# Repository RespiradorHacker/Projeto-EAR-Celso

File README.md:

# e-AR (EAR) PROJECT - EMERGENCY VENTILATOR
This project was born because of CoVid19 pandemic.
The project Goal is to provide an emergency ventilator system to help CoVid19 serious cases using locally available resources. eAR was designed to meet specifications according to MHRA (UK) - Rapidly Manufactured Ventilator System and inspired by MIT E-Vent (USA) concepts and specs.

This is an OPEN HARDWARE - OPEN SOURCE PROJECT. 

DISCLAIMER: we will NOT take any responsability on devices built using partial or total information from this project. 
Any device used for life support and medical applications must meet all local requirements and they must be homologated by local regulatory agencies in ANY case.

The target is to run an entire ventilation system using an automotive car battery and an O2 can.
The initial project leader is Celso Ken Mori Monteiro, automotive designer with +30 yrs experience on automotive embedded systems
as OEM designer for customers as GM, Ford, VW, Fiat, Mercedes Benz, Scania, Navistar, Marcopolo, Agco...

The technology for first PCBs was downsized due to components availability in emerging countries so distributed production could be achieved even in small brazilian towns. The electronic parts are:
- PTH components
- Single-sided PCB, obtainable even by DIYs. 

Besides inclusive concept there is also a FR4 SMT version available for volume production.

Basic concepts:
- External FIO2 O2 + AIR mixer based on timed mechanical truck air valves and plastic bag container
- AMBU smasher based on car window motor due to availabilty and great mechanical characteristics. Motor reversion is necessary to allow dinamic changes of BPM, Tidal Volume, pressure ramping, I/E Ratio and Plateau Hold Time without ANY mechanical change.
- ECU based on Arduino Pro Mini (the most available in emerging countries) and SPI based IO expension
- 2 motor drive options: relay (need second adjustable supply or buck) and PWM driven mosfet driver

Project Evolution:
- full HW schematics and system component's description available on "EAR System Developer's HW Guide", portuguese only version
- PCB Gerbers available, Single Side PTH version, Motor driver on relay option only. Time and size were underestimated because we no longer use these old technologies. Released on March 30, 2020.
- Mech prototype phase 2 aproved, torque is OK and current is low.
- Gerbers of single sided boards on PTH components published on March 30, 2020. Time and size were underestimated because we no longer use these old technologies. 
- EAR System Developer's SW Guide released on March 30, 2020.
- Functional electronics prototype built and delivered on April 2, 2020. No changes in PCBs are necessary except hardware end-of-courses provided for EAR ECU Motor Driver Board. Test driven by firmware FW00 - focused on HW testing only. Reads input pots, control motor with reversal action, measures motor current and tests IO expansion board. All items are functional.
- FW00 published in April 3, 2020.
- Added Mosfet-based PWM Motor Driver and Absolute position sensor using a car fuel level sensor.
- First working mechanical+electrical prototype delivered in April 6, 2020.
- Added Pressure Sensor in April 7, 2020. First artificial lung is a balloon so first pressure profile was obtained. It Sounds promising.
- Firmware controls Tidal Volume and BPM according to Set Potentiometers. First functional firmware produce variable pressure ramps as needed, FW met 8-30 BPM dynamic range specification.
- Added motor cutoff in inspiratory phase according to pressure preset on pot Overpressure Threshold within 1cm H20 resolution.
- Added full mechanical design for functional AMBU compressing ARM in April 11, 2020
- Added in April 12, 2020: Motor Driver, mosfet NN version. Full Kicad design with schematics, PCB and Gerbers.
- Added in April 12,2020: eAR External watchdog Timer to increase eAR reliability. Full Eagle design with schematics, PCB and Gerbers.
- Added in April 13,2020: I/E selection (1:1, 1:2, 1:3 and 1:4) and Plateau Hold Time selection (150, 250, 500 and 1000ms hold on Plateau)
- Added in April 13,2020: Gol G3 tank level float sensor added as absolute position sensor. Increased linearity, resolution and availability
- Mech proto 3.2 added ball bearing in compression arm, currently performing cycling tests
- Added in April 15,2020; eAR Pressure sensor Board Design and PCB, MPX5010DP supported
- Added in April 21,2020: 10x10cm FR4 SMT single PCB design for volume production, verified design, send to production
- Added in April 21,2020: Mechanical proto 3.2 drawings delivered, functional design
- April 30, 2004: eAR FR4 Single-Board PCBs arrived, courtesy from Digicart/SC
- May 1st, 2020: eAR system reached 14 days of 24/7 operation, with 403,412 beathing cycles completed. eAR met minimum durability MHRA (UK) Spec with a prototype built on MDF, a window lift BDC motor and a 20-yrs-old chevy tank float sensor
- May 5, 2020: Multiple pressure sensor added, allowing almost any kind of linear pressure sensor to be connected to eAR system, including MPX5010, MPX10 almost all versions and packages including MPVZ and MP3V and experimental ultra-low-cost MPS20N0040D-S sensor
- May 12, 2020: Integrated EAR ECU tested, functional test OK. Some minor drilling errors corrected, some improvements done and new PCB generated. New mosfet driver option added in firmware as needed. Some components changed values due to standardization effort to ease production. eAR electronics is ready for mass production.
- May 23, 2020: Added first steel based eAR mechanical design, by Ricardo Suzuki. Arm sensor changed to DS 1901 non-contact TPS. 
- June 1st, 2020: Added R2 of mechanical design in two verions, geared arm and 4-linked-bars by Ricardo Suzuki

Pending:
- Software reliability improvements.
- Assisted Ventilation Firmware on hold. It can delay ANVISA aproval when requested.

Special thanks to all people that made this project real!
It's impossible to list all names involved, I apologize for forgetting someone.
The partial list follows:

Project Contributors, as they have joined this project
- Joannes Berque (FR): first design idea.
- Celso Monteiro: eletronics and firmware design, system conception and documentation.
- Diego Padilha and Lucas Pianizzer: electronics and mechanical design+prototyping. 
- Marcelo Pires: electronic CAD, schematics capture & PCB Design.
- Nicolai Rutkevich: mechanical concepts.
- Bruno Afogliatto: decontamination concepts.
- Gustavo Ortenzi: motor drive alteratives.
- Ricardo Suzuki: system concepts and mechanical design.
- Rodrigo Azevedo: organized Github Project.
- Douglas Esteves: interface with other projects.
- João Cardoso and Leonardo Afonso: Kicad Capture for Open Hardware.
- Andre Novelli e Victor Acioly: AMBU bags replacement.
- Flavio Alves: GUI design
- David Loos: electronics assembly

References:
- MIT E-Vent: human requirements and system conception ideas.
- MHRA (UK) Rapidly Manufactured Ventilator System

Healthcare professionals involved:
- Angelica Mammana M.D. helped stablishing specs and performed crytical analysis.
- Fernando Machado M.D. was the first contributing doctor.
- Lucio Flavio M.D.
- Ana Teresa Gama.

Project supporters:
- Fabio Knihs.
- Norberto Tomio.
- Gabriel Casagrande.
- Ivandro Ceccato.

Thanks to my family, special thanks to my dear wife Tissa and my children Joana, Gustavo and Leonardo, for their unlimited support and to all the people that prayed for this project, and God that inspired and guided me all the time.

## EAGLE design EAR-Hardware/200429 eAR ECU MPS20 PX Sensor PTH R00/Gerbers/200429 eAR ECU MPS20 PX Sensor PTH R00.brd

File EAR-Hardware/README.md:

# EAR ECU
Projeto iniciado por Celso Monteiro

- released RDSV200329 EAR System Developer's HW Guide PTBR R00
- This document has details on EAR ECU hardware and its components
- OPEN HARDWARE

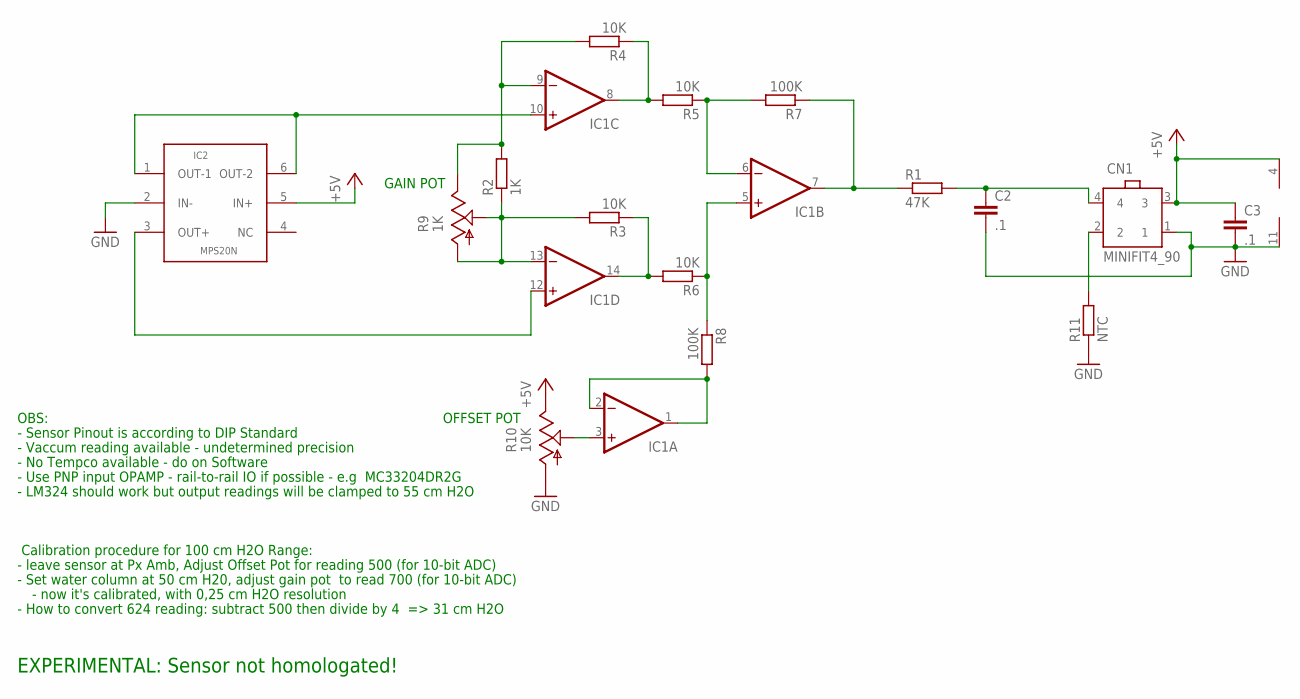
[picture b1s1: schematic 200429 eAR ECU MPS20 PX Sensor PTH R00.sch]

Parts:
C2, C3: .1; C050-025X075
CN1: MINIFIT4_90
IC1: LM324N; DIL14
IC2: MPS20N; DIL6-WIDE
R1: 47K; 0207/10
R2: 1K; 0207/10
R3, R4, R5, R6: 10K; 0207/10
R7, R8: 100K; 0207/10
R9: 1K; B64Y
R10: 10K; B64Y
R11: NTC; R0805W

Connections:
+5V: C3.1, CN1.3, IC1.4 (V+), IC2.5 (IN+), R10.E
GND: C2.2, C3.2, CN1.1, IC1.11 (V-), IC2.2 (IN-), R10.A, R11.1
unnamed: IC1.10 (+IN), IC2.1 (OUT-1), IC2.6 (OUT-2)
unnamed: C2.1, CN1.4, R1.2
unnamed: IC1.12 (+IN), IC2.3 (OUT+)
unnamed: IC1.9 (-IN), R2.2, R4.2, R9.E
unnamed: IC1.13 (-IN), R2.1, R3.2, R9.A, R9.S
unnamed: IC1.7 (OUT), R1.1, R7.1
unnamed: IC1.8 (OUT), R4.1, R5.2
unnamed: IC1.14 (OUT), R3.1, R6.2
unnamed: IC1.3 (+IN), R10.S
unnamed: IC1.6 (-IN), R5.1, R7.2
unnamed: IC1.5 (+IN), R6.1, R8.1
unnamed: CN1.2, R11.2
unnamed: IC1.1 (OUT), IC1.2 (-IN), R8.2

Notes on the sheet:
OBS:
Calibration procedure for 100 cm H2O Range:
- leave sensor at Px Amb, Adjust Offset Pot for reading 500 (for 10-bit ADC)
- Set water column at 50 cm H20, adjust gain pot to read 700 (for 10-bit ADC)
- now it's calibrated, with 0,25 cm H2O resolution
- How to convert 624 reading: subtract 500 then divide by 4 => 31 cm H2O
- Sensor Pinout is according to DIP Standard
GAIN POT
OFFSET POT
- Vaccum reading available - undetermined precision
- No Tempco available - do on Software
- Use PNP input OPAMP - rail-to-rail IO if possible - e.g MC33204DR2G
- LM324 should work but output readings will be clamped to 55 cm H2O
EXPERIMENTAL: Sensor not homologated!

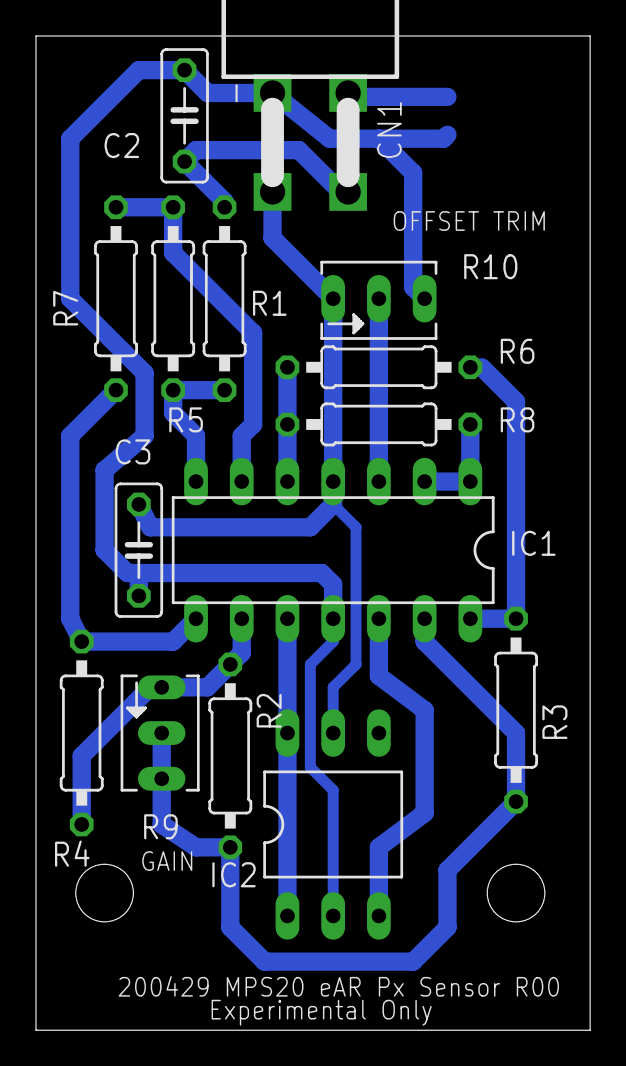
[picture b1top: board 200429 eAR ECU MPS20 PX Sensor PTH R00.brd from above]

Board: 2 copper layers, 30.8 x 55.2 mm, 16 parts (1 on the bottom side), 15 nets.

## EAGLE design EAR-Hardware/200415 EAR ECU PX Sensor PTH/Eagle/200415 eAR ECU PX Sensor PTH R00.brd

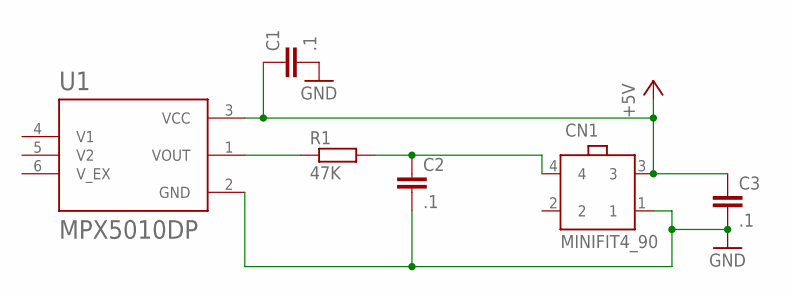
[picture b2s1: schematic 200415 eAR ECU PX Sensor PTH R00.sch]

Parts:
C1, C2, C3: .1; C050-025X075
CN1: MINIFIT4_90
R1: 47K; 0207/10
U1: MPX5010DP; XDCR_MPX5010DP

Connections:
+5V: C1.1, C3.1, CN1.3, U1.3 (VCC)
GND: C1.2, C2.2, C3.2, CN1.1, U1.2 (GND)
unnamed: C2.1, CN1.4, R1.2
unnamed: R1.1, U1.1 (VOUT)

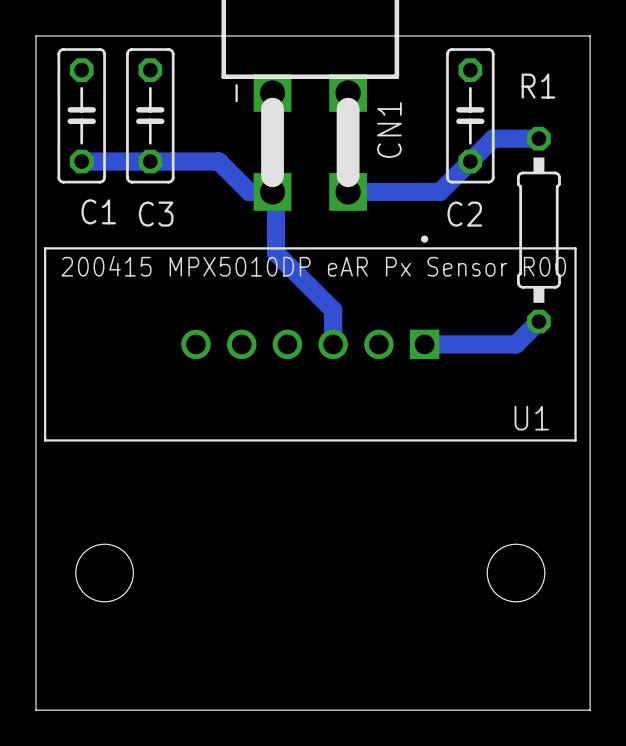
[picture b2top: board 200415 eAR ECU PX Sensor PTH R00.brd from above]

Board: 2 copper layers, 30.8 x 37.5 mm, 6 parts (0 on the bottom side), 4 nets.

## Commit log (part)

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2020-03-22 Arquivos iniciais criados por Celso Monteiro
2020-03-23 Atualização de RDSV Celso Monteiro
2020-03-23 Dirs Specs Hardware e Software Celso
2020-03-23 Organizacao dirs pedido Celso
2020-03-23 Renomeando dirs a pedido Celso
2020-03-23 Esboços movidos para pasta Hardware
2020-03-29 EAR HW Guide por Celso Monteiro
2020-03-29 Update README.md
    Updated EAR PROJECT description
2020-03-30 Add files via upload
    EAR ECU Boards: schematics and Gerbers for CPU, Expansion Board and Motor Driver-Relay Option
2020-03-30 Add files via upload
    3D visualization of boards, required Acrobat Reader DC
2020-03-30 Add files via upload
    Basic EAR ECU Firmware for testing and modeling purposes
2020-04-03 Simple simulator for eAR ECU firmware development
    This simple simulator allows running EAR ECU basic functions:
    - reads pots as real ones
    - FlexLed (serial debug) is active and returns reasonable values for implemented functions
    - switched pot simulates flat motor current
    - motor machine status is shown
2020-04-03 First eAR ECU Prototype RUN
    Low resources POC worked! eAR ECU inclusive design is made on 3 single sided PCBs with shelf available PTH components connected by IDC connectors (same as old PCs) with retundant vias.
2020-04-03 Revisão inicial de arquitetura
    * Troca de diretório para funcionar no Arduino IDE
    * Inclusão de lib de escalonamento de tarefas
    * Ajuste do loop principal como atividade periodica
2020-04-03 Refatoração do timer
    Troca de lib
2020-04-03 changed timer interrupt from 100ms to 10ms
2020-04-05 eAR Mechanical Proto3 Operation Videos
    4V operation, unloaded AMBU compression, thanks Diego, Lucas for protos, Nicolai for hints
2020-04-06 eAR Mechanical Proto3 on PWM and Absolute Sensor
    New mosfet based PWM motor driver, absolute arm position sensor based on car tank sensor, working fine!
2020-04-07 Added Disclaimer
2020-04-07 Calibrating Pressure Sensor on H2O cm using H2O cm
    On your nearby hardware store you'll find all you need to build a simple H2O calibration system for your MEMS tubed pressure sensor. Relative pressure, of course. The second output, attached to an au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
2020-04-07 First Pressure Profile - Video and Scope waveforms
    Added Pressure Sensor MPX5010DP on eAR Pressure port. Best lung we could afford is a ballon. Same PWM profile as before. TEK images: on Top we have position sensor (Car Tank Float Sensor). Bottom is 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
2020-04-08 GUI Sketch added
2020-04-08 Real FlexLed Data for GUI testing purposes
    Same cycle as on previous movie, functional cycles during minutes. FlexLed serial dump was updated to present data for GUI under development. Position sensor is real, Tidal volume is simulated throug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
2020-04-08 eAR ECU - Motor Driver Mosfet NN version
    The Motor Driver - Mosfet NN version uses shelf N-CH low level drive mosfets to drive the motor. These mosfets are used in automotive applications so these semi are very common. Design by Gustavo Ort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
2020-04-10 FW02 prerelease
    Tidal, BPM and other functions working. Restriction on pressures not implemented. Open Loop PWM Lookup table implemented, not tuned. Automatic Lookup Table Generation will be released soon.
2020-04-10 LookUpTable Generator for PWM set as function of Desired Inspiration Ramping Speed.
    LookUpTable Generator for PWM set as function of Desired Inspiration Ramping Speed. It can be used to tune PWM response as a function of desired arm speed in inspiration. Open Loop - first aproach, i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
    It could be used as a generic LookUpTable generator for other purposes.
    As it was built using arduino IDE, there is no need for another compiler, so Arduino Pro Mini is the LookUpTable generator robot.
2020-04-10 eAR works now on limited Pressure, based on OverPx Threshold Pot
    On Inspiration Overpressure, eAR ECU shuts down motor and beeps. Repeatable results on 1 cm H2O resolution.
2020-04-11 Create Mechanical
2020-04-11 Create ARM Project
2020-04-11 Mechanical ARM for eAR - Design by Diego Padilha and Lucas Pianizzer
    Simple fully functional mechanical Arm for eAR ventilator system. It can be prototyped even on MDF. Besides nuts and bolts, only a car window motor and a car tank fuel sensor are necessary
2020-04-11 Added that eAR was designed to meet specifications according to MIT E-Vent (USA) and MHRA (UK) - Rapidly Manufacuted Ventilator System
2020-04-12 Added mechanical design files and Motor Driver - Mosfet NN version with gerbers
2020-04-12 Added External WatchDog Timer - Schematics, boards and Gerbers
    In order to achieve a reasonable level of reliability, a planned external watchdog was developed. Arduino bootloader is not compatible with watchdogs so this part needs to be removed when upgrading e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
2020-04-12 Added External eAR Watchdog Timer
2020-04-12 added designed to meet MIT E-Vent and MHRA (UK) - Rapidly Manufacuted Ventilator System specifications
2020-04-12 Added external watchdog support
    As planned, an external watchdog was added to eAR. Arduino is not reliable enough so this is a MANDATORY add-on. It is focused on restarting when arduino firmware loses control. Signals are generated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
2020-04-13 Added I/E and Plateau Hold Time programming, added Gol G3 tank level float sensor as absolute position sensor
2020-04-14 adds selectable I/E Ratio and Plateau Hold Time
    Switches connected to eAR expanded IO now define I/E ratio (1:1, 1:2, 1:3 and 1:4) and Plateau Hold Time (150, 250, 500ms and 1s)
2020-04-14 added using eAR software
2020-04-15 added Pressure Sensor Board
    The pressure sensor could be integrated in ECU Board but we preferred to have a three-wire cable instead of a long tube so we designed a new board connected to ECU by a 4-way Molex MiniFit Jr connect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
2020-04-15 Added MIT E-Vent Specifications
2020-04-17 Added MHRA reference
2020-04-17 eAR Preliminary Results - design development, performance and BOM cost
    eAR preliminary results are presented showing design evolution, choices, limitations, sucesses and resulting performance data and BOM cost
2020-04-20 changed Respirator for Ventilator
2020-04-20 Set theme jekyll-theme-cayman
2020-04-20 Update project title
2020-04-20 Set base URL for the links
2020-04-20 Force the site title on header
2020-04-20 Try to set page title on header first
2020-04-20 Set the page title
2020-04-21 eAR Integrated ECU FR4 SMT
    eAR Integrated ECU = 10x10cm FR4 SMT board with CPU + EXP Board + Mosfet option Motor Driver + Hardware watchdog. UNVERIFIED.
2020-04-21 included mass production possibility with FR4 SMT Board availability
2020-04-22 revised with minor changes
2020-04-22 eAR Integrated ECU = 10x10cm FR4 SMT board with CPU + EXP Board + Mosfet option Motor Driver + Hardware watchdog. VERIFIED.
    eAR Integrated ECU = 10x10cm FR4 SMT board with CPU + EXP Board + Mosfet option Motor Driver + Hardware watchdog. VERIFIED.
    KiCad generated, with schematics, PCB and 3D. Designed for volume production. Assembled Arduino is an option, ATMega328 can be assembled on board instead.
    PCB Design thanks to Marcelo Pires and Diego Padilha
2020-04-22 eAR Compression Arm for AMBU - prototype 3.2 - functional
    Functional AMBU Compression Arm for eAR System R00. AKA Mech Prototype 3.2, added ball bearings on arm, works even on MDF parts. Uses Mabuchi BDC motor and Gol G3 Tank Float Sensor as absolute arm po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
2020-04-22 added mechanical design R00 - AKA mech proto 3.2
2020-04-29 Added MPS20N0040 EXPERMENTAL Pressure sensor and Tilted Arm position Sensor
    Added MPS20N0040 EXPERMENTAL Pressure sensor due to scarce Homologated pressure sensors. Now we can measure low pressures, even vaccum can be measured due to 1/2 VCC DC bias on new Px Sensor board wi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
    Included new Tilted Arm position Sensor paramenters.
2020-05-03 Set the site title as the default header
2020-05-03 Remove the forced page title
2020-05-03 Update the Join page details
2020-05-03 Update the Join link in Contact page
2020-05-03 added project progress: eAR met MHRA durability, Multisensor pressure module added.
2020-05-03 Explicited Motor reversion benefits: dinamic changes of BPM, Tidal Volume, pressure ramping, etc without ANY mechanical change.
    Explicited that motor reversion is necessary to allow dinamic changes of BPM, Tidal Volume, pressure ramping, I/E Ratio and Plateau Hold Time without ANY mechanical change.
2020-05-12 eAR ECU Integrated R01 - Minor Preproduction Changes - thanks to Diego Padilha
    eAR ECU Integrated R01 - Minor Preproduction Changes
    - Drilling corrections: Varistor, PPTC
    - Resistors: 22K and 47K changed to 100K, 4K7 changed to 10K
    - Bipolar transistors on H Bridge turned from BC807/BC817 to MMBT56 and MMBT06 to increase transient protection
    - Buzzer allow now 5 and 7.5mm pitch types
    - Potentiometers allow now 100 and 200 mils pitch types/models
2020-05-12 eAR on NEW Integrated ECU - H Bridge Motor Driver now runs on N-Channel Mosfets Only
    eAR on NEW Integrated ECU - H Bridge Motor Driver now runs on N-Channel Mosfets Only
    - So far Bridge Motor Driver was based on P and N-Channel Mosfets
    - New integrated electronics bring charge pump N-CH High Side Drivers
    - Optional driver set by #define on SW
    - Functional Test of new electronics is OK!
2020-05-12 Integrated ECU tested OK, minor changes and improvements on PCB and Firmware
2020-05-13 eAR Full set on new integrated ECU
    eAR ECU electronics is ready for mass production.
    - VCV with aditional pressure limiting control was implemented, according to MHRA RMVS 1.d
    - even with MDF mechanics eAR passed minimum 14 days 24hours continuos operation
    We're working on eAR housing to proceed with clinical tests.
2020-05-13 eAR full set with new integrated ECU
    eAR ECU electronics is ready for mass production.
    - VCV with aditional pressure limiting control was implemented, according to MHRA RMVS 1.d
    - even with MDF mechanics eAR passed minimum 14 days 24hours continuos operation
    We're working on eAR housing to proceed with clinical tests.
2020-05-20 EAR System Preliminary Bill of Materials
    EAR System Preliminary Bill of Materials - cost estimation of all components to build the AMBU compression system, including eAR ECU, Pressure Sensor and mechanical parts
2020-05-25 200523 eAR Mech Arm Gear Option - First Steel Version with geared Arm - by Ricardo Suzuki
    This is the first steel version of eAR mechanics, geared arm option, thanks to mechanical designer Ricardo Suzuki. Made mostly on steel sheet parts and reinforced plastic gear.
2020-05-25 200523 eAR Mech Arm Gear Option by Suzuki
    This is the first steel version of eAR mechanics, geared arm option, thanks to mechanical designer Ricardo Suzuki. Made mostly on steel sheet parts and reinforced plastic gear.
2020-05-25 Added first steel based eAR mechanical design, by Ricardo Suzuki. Arm sensor changed to DS 1901 non-contact TPS.
2020-05-26 eAR Presentation Video PTBR - brazilian portuguese audio
    eAR Presentation Video PTBR - brazilian portuguese audio by Ricardo Suzuki.
    - pressure limit functional demo
    - encapsulation target: beginning of june
    - Cost: < R$ 400 + taxes including electronics, motor, mechanics and pressure sensor
2020-06-01 200601 eAR Mechanical Design R2 - Gear and 4-bar linkage options - by Ricardo Suzuki
    200601 eAR Mechanical Design R2 released on Geared and 4-bar linkage options. Geared option is an evolution of the geared arm prototype and 4-bar linkage is a completely new version inspired in Nicol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
2020-06-01 Added R2 of mechanical design in two verions, geared arm and 4-linked-bars by Ricardo Suzuki
